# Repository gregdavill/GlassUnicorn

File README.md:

# Glass Unicorn

## Colection of various dense LED matrix projects

	Project status: Work in progress

## Panel_r0.1
 * 24x24 RGB 2020 LEDs
 * Matrix construction with 4bit wide serial input.
 * Optimised for low cost: ~$15 BOM cost

## Cube_r0.1
 * Aluminium frame to fit the panels in a cube
 * ~64mm square

## Controller_r0.1

    TBD

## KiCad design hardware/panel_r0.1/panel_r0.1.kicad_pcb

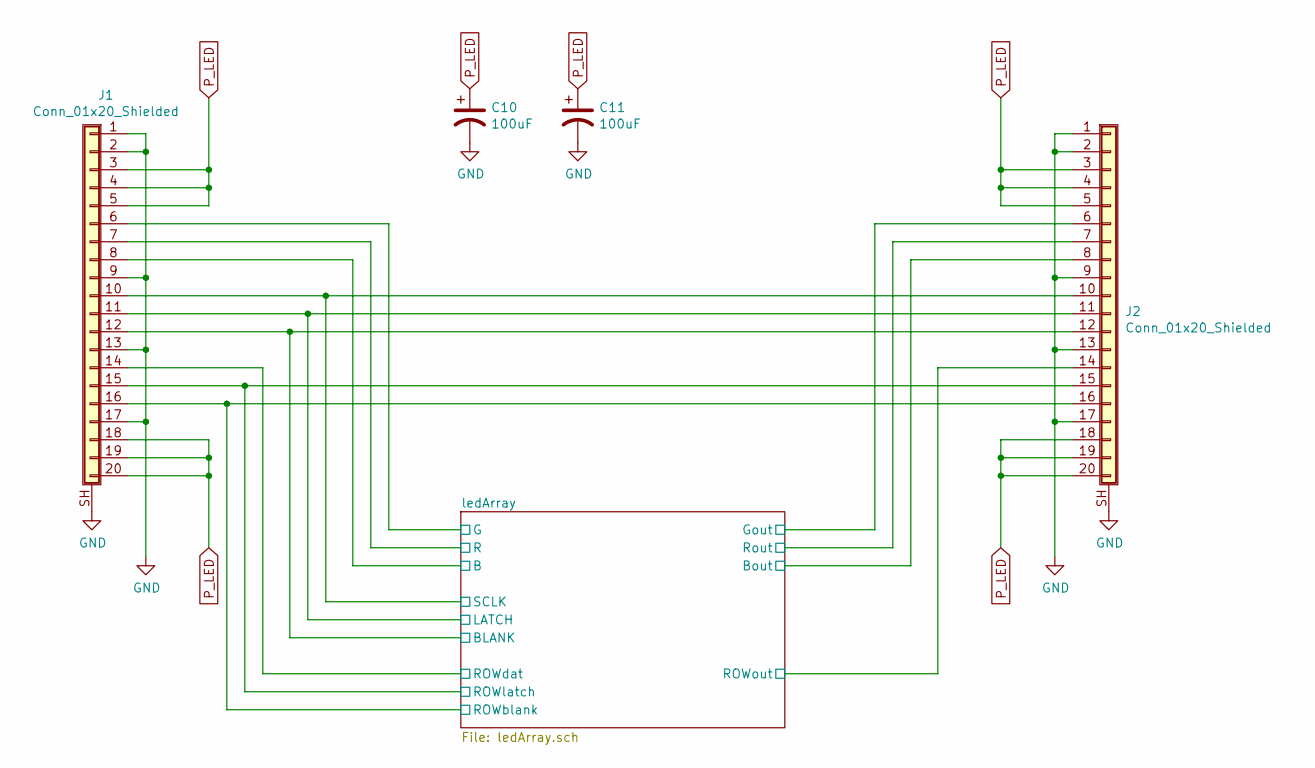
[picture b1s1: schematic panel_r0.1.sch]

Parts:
C10, C11: 100uF; CP_Elec_5x3.9
J1, J2: Conn_01x20_Shielded; FH12-20S-0.5SVA(54)

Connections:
/ledArray/B: J1.8; also elsewhere on the board
/ledArray/BLANK: J1.12, J2.12; also elsewhere on the board
/ledArray/Bout: J2.8; also elsewhere on the board
/ledArray/G: J1.6; also elsewhere on the board
/ledArray/Gout: J2.6; also elsewhere on the board
/ledArray/LATCH: J1.11, J2.11; also elsewhere on the board
/ledArray/R: J1.7; also elsewhere on the board
/ledArray/ROWblank: J1.16, J2.16; also elsewhere on the board
/ledArray/ROWdat: J1.14; also elsewhere on the board
/ledArray/ROWlatch: J1.15, J2.15; also elsewhere on the board
/ledArray/ROWout: J2.14; also elsewhere on the board
/ledArray/Rout: J2.7; also elsewhere on the board
/ledArray/SCLK: J1.10, J2.10; also elsewhere on the board
GND: C10.2, C11.2, J1.1, J1.2, J1.9, J1.13, J1.17, J1.SH (Shield), J2.1, J2.2, J2.9, J2.13, J2.17, J2.SH (Shield); also elsewhere on the board
P_LED: C10.1, C11.1, J1.3, J1.4, J1.5, J1.18, J1.19, J1.20, J2.3, J2.4, J2.5, J2.18, J2.19, J2.20; also elsewhere on the board

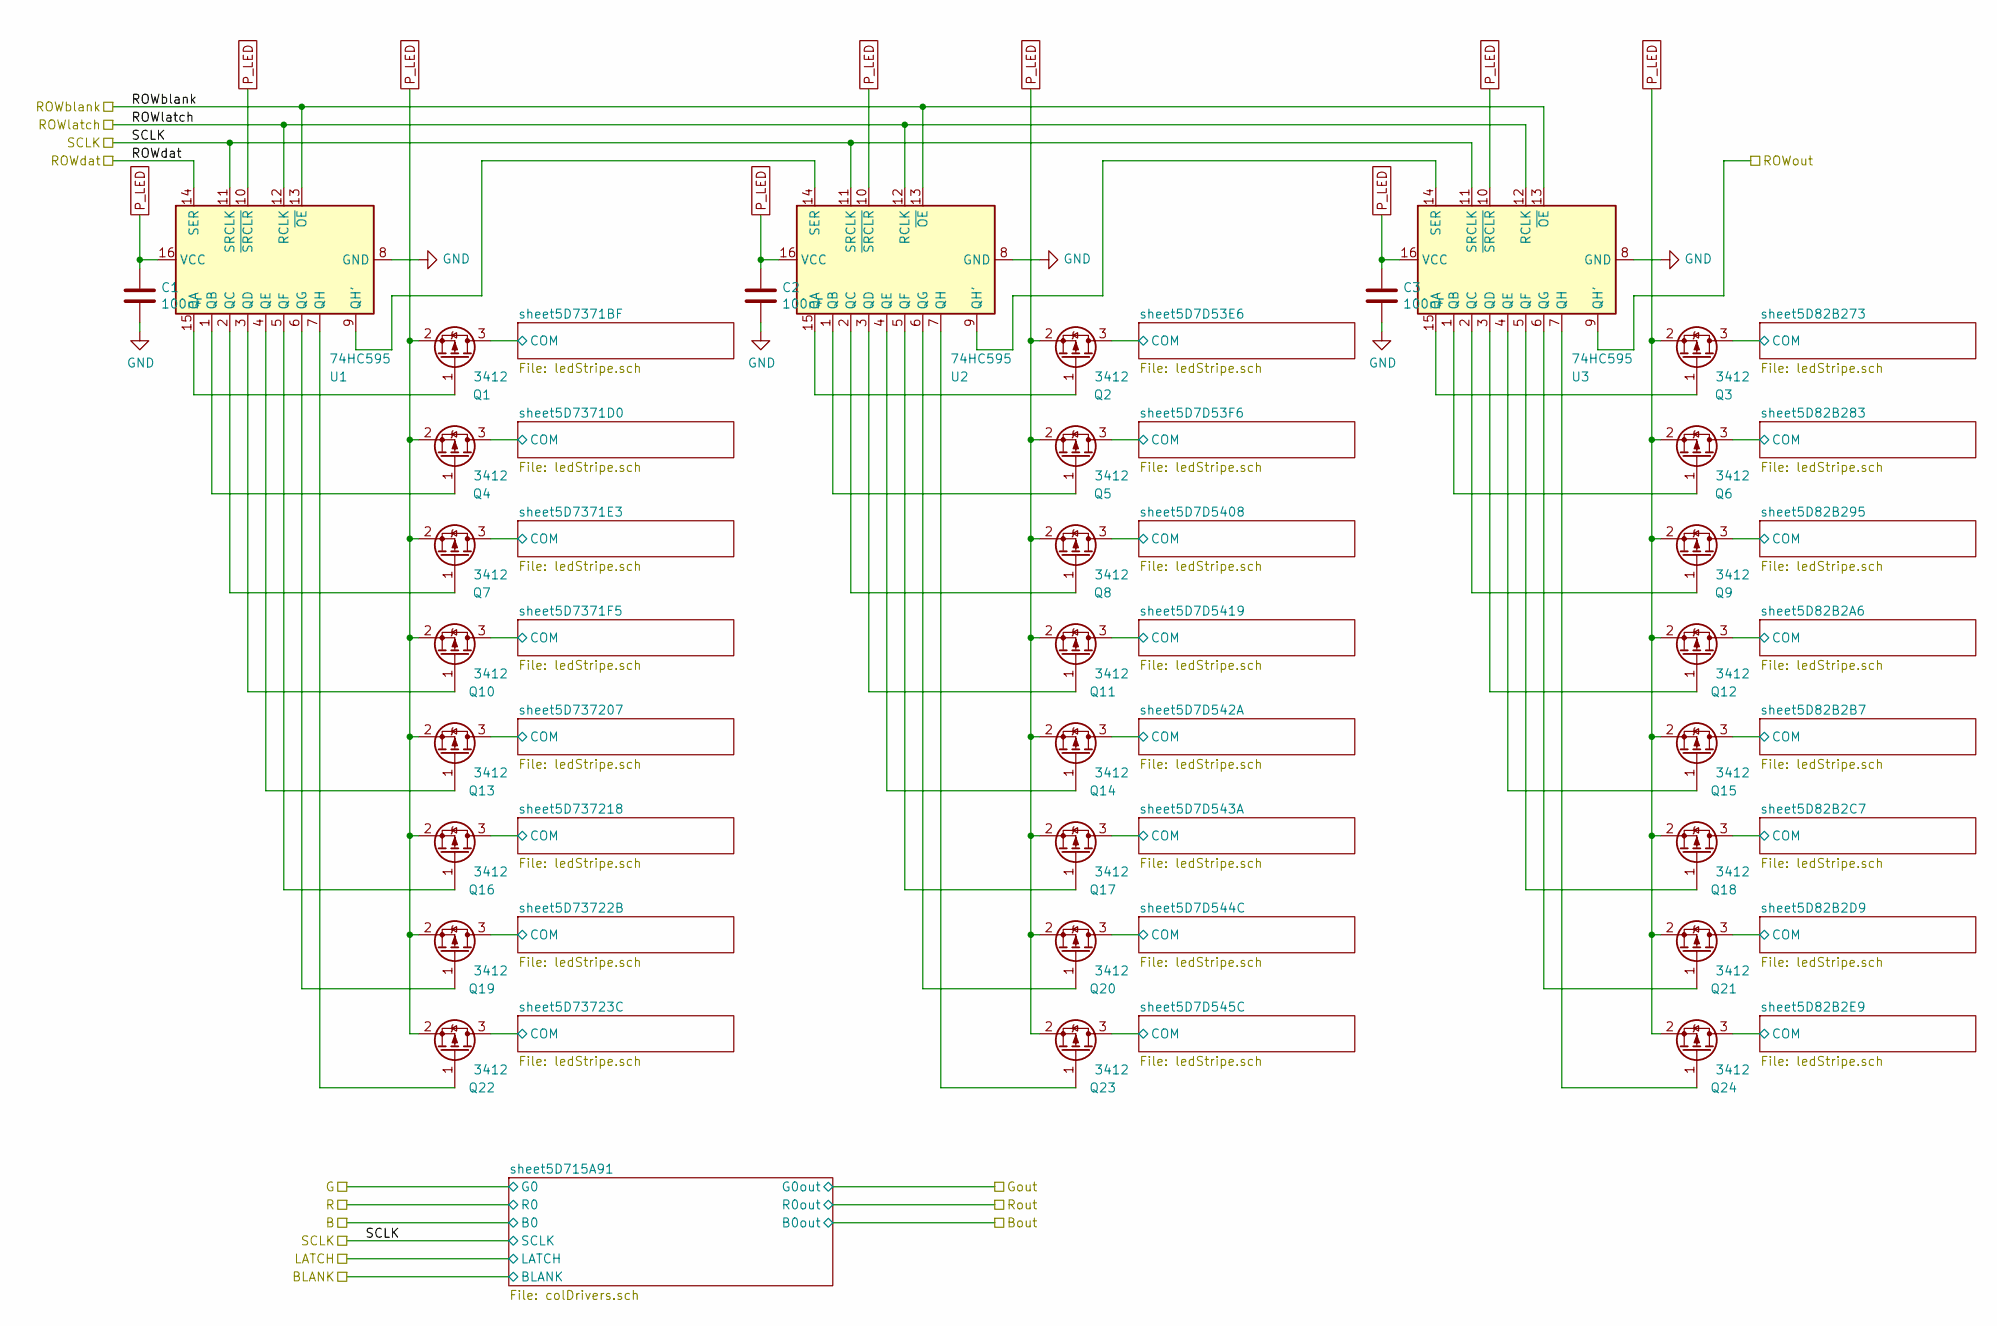
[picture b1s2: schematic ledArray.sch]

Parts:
C1, C2, C3: 100nF; C_0603_1608Metric
Q1, Q2, Q3, Q4, Q5, Q6, Q7, Q8, Q9, Q10, Q11, Q12, Q13, Q14, Q15, Q16, Q17, Q18, Q19, Q20, Q21, Q22, Q23, Q24: 3412; SOT-23
U1, U2, U3: 74HC595; SOIC-16_3.9x9.9mm_P1.27mm

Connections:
/ledArray/ROWblank: U1.13 (~OE), U2.13 (~OE), U3.13 (~OE); also elsewhere on the board
/ledArray/ROWdat: U1.14 (SER); also elsewhere on the board
/ledArray/ROWlatch: U1.12 (RCLK), U2.12 (RCLK), U3.12 (RCLK); also elsewhere on the board
/ledArray/ROWout: U3.9 (QH'); also elsewhere on the board
/ledArray/SCLK: U1.11 (SRCLK), U2.11 (SRCLK), U3.11 (SRCLK); also elsewhere on the board
/ledArray/sheet5D7D53E6/COM: Q2.3 (D); also elsewhere on the board
/ledArray/sheet5D7D53F6/COM: Q5.3 (D); also elsewhere on the board
/ledArray/sheet5D7D542A/COM: Q14.3 (D); also elsewhere on the board
/ledArray/sheet5D7D543A/COM: Q17.3 (D); also elsewhere on the board
/ledArray/sheet5D7D544C/COM: Q20.3 (D); also elsewhere on the board
/ledArray/sheet5D7D545C/COM: Q23.3 (D); also elsewhere on the board
/ledArray/sheet5D7D5408/COM: Q8.3 (D); also elsewhere on the board
/ledArray/sheet5D7D5419/COM: Q11.3 (D); also elsewhere on the board
/ledArray/sheet5D82B2A6/COM: Q12.3 (D); also elsewhere on the board
/ledArray/sheet5D82B2B7/COM: Q15.3 (D); also elsewhere on the board
/ledArray/sheet5D82B2C7/COM: Q18.3 (D); also elsewhere on the board
/ledArray/sheet5D82B2D9/COM: Q21.3 (D); also elsewhere on the board
/ledArray/sheet5D82B2E9/COM: Q24.3 (D); also elsewhere on the board
/ledArray/sheet5D82B273/COM: Q3.3 (D); also elsewhere on the board
/ledArray/sheet5D82B283/COM: Q6.3 (D); also elsewhere on the board
/ledArray/sheet5D82B295/COM: Q9.3 (D); also elsewhere on the board
/ledArray/sheet5D7371BF/COM: Q1.3 (D); also elsewhere on the board
/ledArray/sheet5D7371D0/COM: Q4.3 (D); also elsewhere on the board
/ledArray/sheet5D7371E3/COM: Q7.3 (D); also elsewhere on the board
/ledArray/sheet5D7371F5/COM: Q10.3 (D); also elsewhere on the board
/ledArray/sheet5D73722B/COM: Q19.3 (D); also elsewhere on the board
/ledArray/sheet5D73723C/COM: Q22.3 (D); also elsewhere on the board
/ledArray/sheet5D737207/COM: Q13.3 (D); also elsewhere on the board
/ledArray/sheet5D737218/COM: Q16.3 (D); also elsewhere on the board
GND: C1.2, C2.2, C3.2, U1.8 (GND), U2.8 (GND), U3.8 (GND); also elsewhere on the board
unnamed: Q1.1 (G), U1.15 (QA)
unnamed: Q2.1 (G), U2.15 (QA)
unnamed: Q3.1 (G), U3.15 (QA)
unnamed: Q4.1 (G), U1.1 (QB)
unnamed: Q5.1 (G), U2.1 (QB)
unnamed: Q6.1 (G), U3.1 (QB)
unnamed: Q7.1 (G), U1.2 (QC)
unnamed: Q8.1 (G), U2.2 (QC)
unnamed: Q9.1 (G), U3.2 (QC)
unnamed: Q10.1 (G), U1.3 (QD)
unnamed: Q11.1 (G), U2.3 (QD)
unnamed: Q12.1 (G), U3.3 (QD)
unnamed: Q13.1 (G), U1.4 (QE)
unnamed: Q14.1 (G), U2.4 (QE)
unnamed: Q15.1 (G), U3.4 (QE)
unnamed: Q16.1 (G), U1.5 (QF)
unnamed: Q17.1 (G), U2.5 (QF)
unnamed: Q18.1 (G), U3.5 (QF)
unnamed: Q19.1 (G), U1.6 (QG)
unnamed: Q20.1 (G), U2.6 (QG)
unnamed: Q21.1 (G), U3.6 (QG)
unnamed: Q22.1 (G), U1.7 (QH)
unnamed: Q23.1 (G), U2.7 (QH)
unnamed: Q24.1 (G), U3.7 (QH)
unnamed: U1.9 (QH'), U2.14 (SER)
unnamed: U2.9 (QH'), U3.14 (SER)
P_LED: C1.1, C2.1, C3.1, Q1.2 (S), Q2.2 (S), Q3.2 (S), Q4.2 (S), Q5.2 (S), Q6.2 (S), Q7.2 (S), Q8.2 (S), Q9.2 (S), Q10.2 (S), Q11.2 (S), Q12.2 (S), Q13.2 (S), Q14.2 (S), Q15.2 (S), Q16.2 (S), Q17.2 (S), Q18.2 (S), Q19.2 (S), Q20.2 (S), Q21.2 (S), Q22.2 (S), Q23.2 (S), Q24.2 (S), U1.10 (~SRCLR), U1.16 (VCC), U2.10 (~SRCLR), U2.16 (VCC), U3.10 (~SRCLR), U3.16 (VCC); also elsewhere on the board

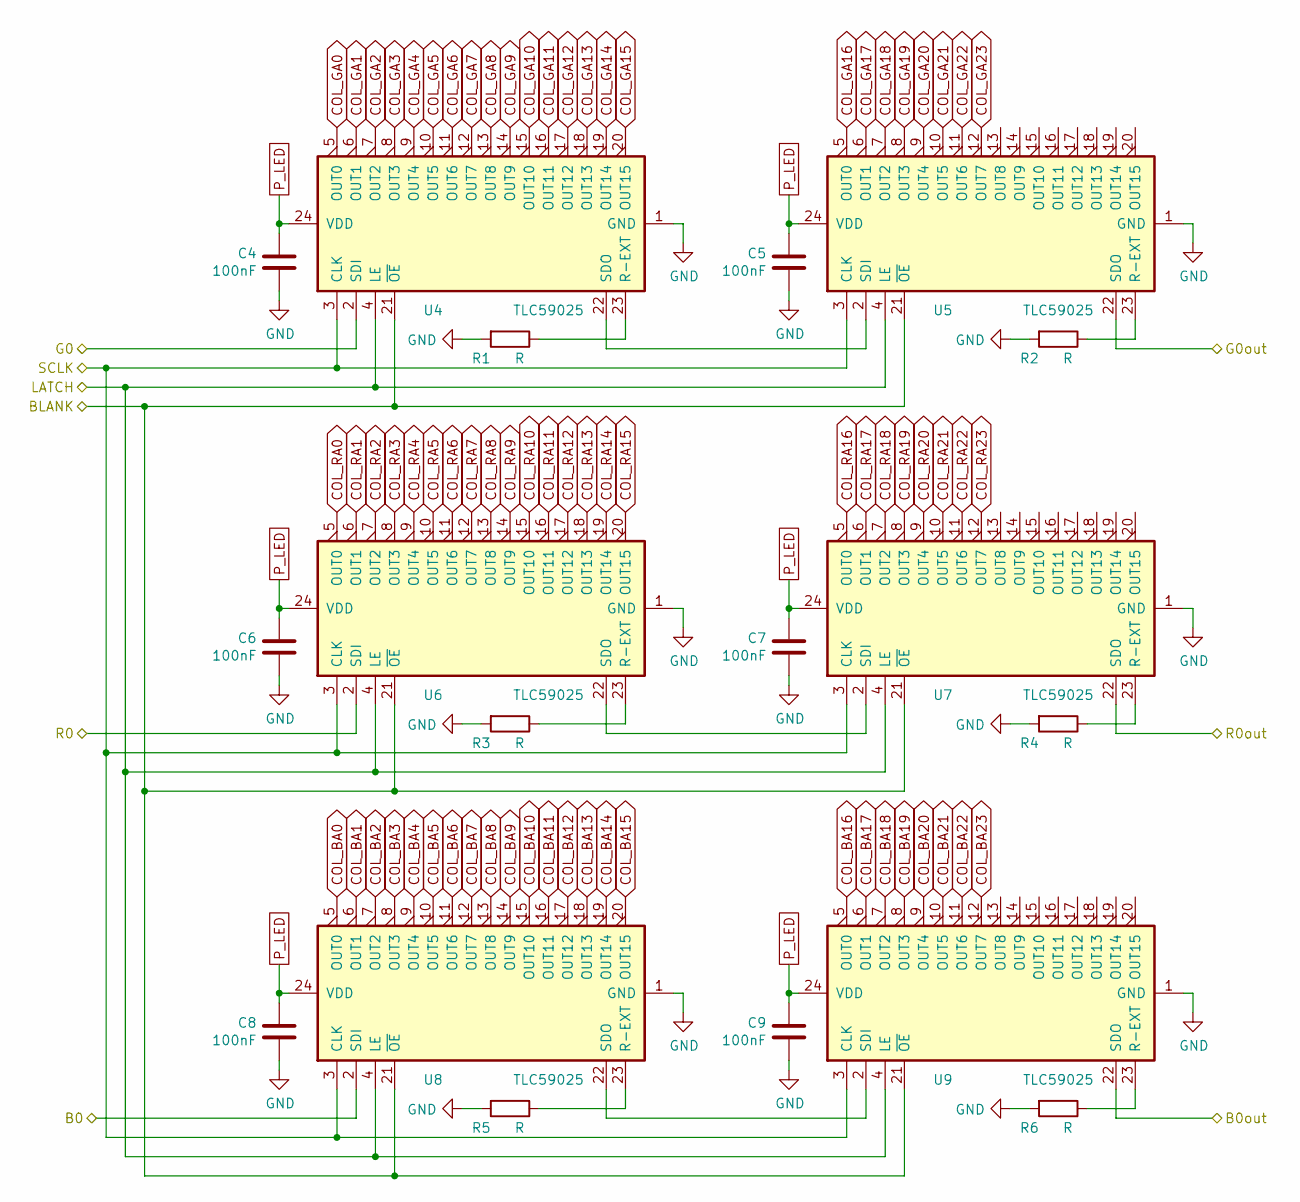
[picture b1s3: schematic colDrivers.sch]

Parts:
C4, C5, C6, C7, C8, C9: 100nF; C_0603_1608Metric
R1, R2, R3, R4, R5, R6: R; R_0603_1608Metric
U4, U5, U6, U7, U8, U9: TLC59025; SSOP-24_3.9x8.7mm_P0.635mm

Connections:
/ledArray/B: U8.2 (SDI); also elsewhere on the board
/ledArray/BLANK: U4.21 (~OE), U5.21 (~OE), U6.21 (~OE), U7.21 (~OE), U8.21 (~OE), U9.21 (~OE); also elsewhere on the board
/ledArray/Bout: U9.22 (SDO); also elsewhere on the board
/ledArray/G: U4.2 (SDI); also elsewhere on the board
/ledArray/Gout: U5.22 (SDO); also elsewhere on the board
/ledArray/LATCH: U4.4 (LE), U5.4 (LE), U6.4 (LE), U7.4 (LE), U8.4 (LE), U9.4 (LE); also elsewhere on the board
/ledArray/R: U6.2 (SDI); also elsewhere on the board
/ledArray/Rout: U7.22 (SDO); also elsewhere on the board
/ledArray/SCLK: U4.3 (CLK), U5.3 (CLK), U6.3 (CLK), U7.3 (CLK), U8.3 (CLK), U9.3 (CLK); also elsewhere on the board
COL_BA0: U8.5 (OUT0); also elsewhere on the board
COL_BA1: U8.6 (OUT1); also elsewhere on the board
COL_BA2: U8.7 (OUT2); also elsewhere on the board
COL_BA3: U8.8 (OUT3); also elsewhere on the board
COL_BA4: U8.9 (OUT4); also elsewhere on the board
COL_BA5: U8.10 (OUT5); also elsewhere on the board
COL_BA6: U8.11 (OUT6); also elsewhere on the board
COL_BA7: U8.12 (OUT7); also elsewhere on the board
COL_BA8: U8.13 (OUT8); also elsewhere on the board
COL_BA9: U8.14 (OUT9); also elsewhere on the board
COL_BA10: U8.15 (OUT10); also elsewhere on the board
COL_BA11: U8.16 (OUT11); also elsewhere on the board
COL_BA12: U8.17 (OUT12); also elsewhere on the board
COL_BA13: U8.18 (OUT13); also elsewhere on the board
COL_BA14: U8.19 (OUT14); also elsewhere on the board
COL_BA15: U8.20 (OUT15); also elsewhere on the board
COL_BA16: U9.5 (OUT0); also elsewhere on the board
COL_BA17: U9.6 (OUT1); also elsewhere on the board
COL_BA18: U9.7 (OUT2); also elsewhere on the board
COL_BA19: U9.8 (OUT3); also elsewhere on the board
COL_BA20: U9.9 (OUT4); also elsewhere on the board
COL_BA21: U9.10 (OUT5); also elsewhere on the board
COL_BA22: U9.11 (OUT6); also elsewhere on the board
COL_BA23: U9.12 (OUT7); also elsewhere on the board
COL_GA0: U4.5 (OUT0); also elsewhere on the board
COL_GA1: U4.6 (OUT1); also elsewhere on the board
COL_GA2: U4.7 (OUT2); also elsewhere on the board
COL_GA3: U4.8 (OUT3); also elsewhere on the board
COL_GA4: U4.9 (OUT4); also elsewhere on the board
COL_GA5: U4.10 (OUT5); also elsewhere on the board
COL_GA6: U4.11 (OUT6); also elsewhere on the board
COL_GA7: U4.12 (OUT7); also elsewhere on the board
COL_GA8: U4.13 (OUT8); also elsewhere on the board
COL_GA9: U4.14 (OUT9); also elsewhere on the board
COL_GA10: U4.15 (OUT10); also elsewhere on the board
COL_GA11: U4.16 (OUT11); also elsewhere on the board
COL_GA12: U4.17 (OUT12); also elsewhere on the board
COL_GA13: U4.18 (OUT13); also elsewhere on the board
COL_GA14: U4.19 (OUT14); also elsewhere on the board
COL_GA15: U4.20 (OUT15); also elsewhere on the board
COL_GA16: U5.5 (OUT0); also elsewhere on the board
COL_GA17: U5.6 (OUT1); also elsewhere on the board
COL_GA18: U5.7 (OUT2); also elsewhere on the board
COL_GA19: U5.8 (OUT3); also elsewhere on the board
COL_GA20: U5.9 (OUT4); also elsewhere on the board
COL_GA21: U5.10 (OUT5); also elsewhere on the board
COL_GA22: U5.11 (OUT6); also elsewhere on the board
COL_GA23: U5.12 (OUT7); also elsewhere on the board
COL_RA0: U6.5 (OUT0); also elsewhere on the board
COL_RA1: U6.6 (OUT1); also elsewhere on the board
COL_RA2: U6.7 (OUT2); also elsewhere on the board
COL_RA3: U6.8 (OUT3); also elsewhere on the board
COL_RA4: U6.9 (OUT4); also elsewhere on the board
COL_RA5: U6.10 (OUT5); also elsewhere on the board
COL_RA6: U6.11 (OUT6); also elsewhere on the board
COL_RA7: U6.12 (OUT7); also elsewhere on the board
COL_RA8: U6.13 (OUT8); also elsewhere on the board
COL_RA9: U6.14 (OUT9); also elsewhere on the board
COL_RA10: U6.15 (OUT10); also elsewhere on the board
COL_RA11: U6.16 (OUT11); also elsewhere on the board
COL_RA12: U6.17 (OUT12); also elsewhere on the board
COL_RA13: U6.18 (OUT13); also elsewhere on the board
COL_RA14: U6.19 (OUT14); also elsewhere on the board
COL_RA15: U6.20 (OUT15); also elsewhere on the board
COL_RA16: U7.5 (OUT0); also elsewhere on the board
COL_RA17: U7.6 (OUT1); also elsewhere on the board
COL_RA18: U7.7 (OUT2); also elsewhere on the board
COL_RA19: U7.8 (OUT3); also elsewhere on the board
COL_RA20: U7.9 (OUT4); also elsewhere on the board
COL_RA21: U7.10 (OUT5); also elsewhere on the board
COL_RA22: U7.11 (OUT6); also elsewhere on the board
COL_RA23: U7.12 (OUT7); also elsewhere on the board
GND: C4.2, C5.2, C6.2, C7.2, C8.2, C9.2, R1.2, R2.2, R3.2, R4.2, R5.2, R6.2, U4.1 (GND), U5.1 (GND), U6.1 (GND), U7.1 (GND), U8.1 (GND), U9.1 (GND); also elsewhere on the board
unnamed: R1.1, U4.23 (R-EXT)
unnamed: R2.1, U5.23 (R-EXT)
unnamed: R3.1, U6.23 (R-EXT)
unnamed: R4.1, U7.23 (R-EXT)
unnamed: R5.1, U8.23 (R-EXT)
unnamed: R6.1, U9.23 (R-EXT)
unnamed: U4.22 (SDO), U5.2 (SDI)
unnamed: U6.22 (SDO), U7.2 (SDI)
unnamed: U8.22 (SDO), U9.2 (SDI)
P_LED: C4.1, C5.1, C6.1, C7.1, C8.1, C9.1, U4.24 (VDD), U5.24 (VDD), U6.24 (VDD), U7.24 (VDD), U8.24 (VDD), U9.24 (VDD); also elsewhere on the board
